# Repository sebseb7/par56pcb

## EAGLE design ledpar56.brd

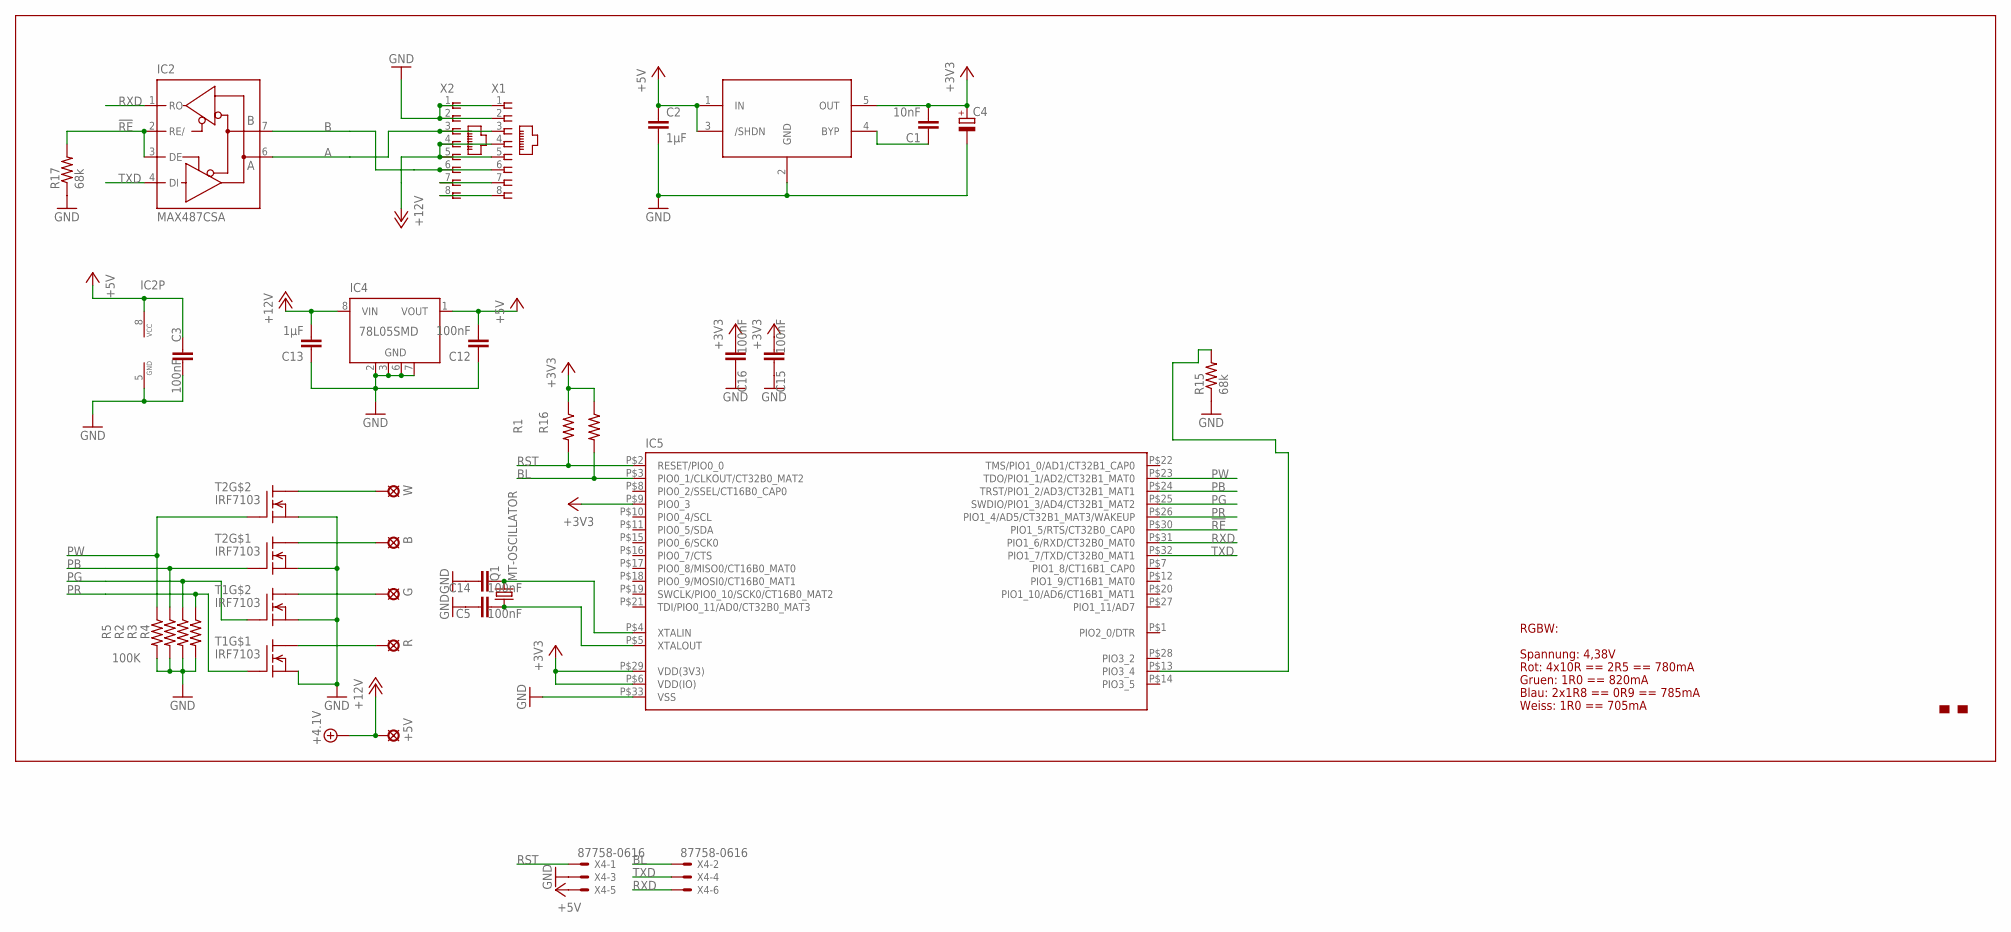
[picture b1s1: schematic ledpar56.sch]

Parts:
+5V: SE14
B: SE14
C1: 10nF; C0402
C2, C13: 1µF; 0805
C3, C5, C12, C14, C15, C16: 100nF; 0402-CAP
C4: CPOL-EUSMCA; SMC_A
G: SE14
IC1: LT1761; SOT23-5L
IC2: MAX487CSA; SO08
IC4: 78L05SMD; SO08
IC5: LPC1113/4_QFN; HVQFN33-7X7
Q1: MT-OSCILLATOR; MT
R: SE14
R1, R2, R3, R4, R5, R16: 100K; 0402-RES
R15, R17: 68k; 0402-RES
T1, T2: IRF7103; SO-8
U$1: MAKE-DD_LOGO'PROMPT'; MAKE-DD_LOGO_PROMPT
W: SE14
X1, X2: RJ45-8L-B; RJ45-NO-SHIELD
X4: 87758-0616

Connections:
!RE: IC2.2 (RE/), IC2.3 (DE), IC5.P$30 (PIO1_5/RTS/CT32B0_CAP0), R17.2
+3V3: C1.2, C4.+, C15.2, C16.2, IC1.5 (OUT), IC5.P$6 (VDD(IO)), IC5.P$9 (PIO0_3), IC5.P$29 (VDD(3V3)), R1.1, R16.1
+5V: C2.1, C3.1, C12.2, IC1.1 (IN), IC1.3 (/SHDN), IC2.8 (VCC), IC4.1 (VOUT), X4.5
+12V: +5V.MP, C13.2, IC4.8 (VIN), X1.4, X1.5, X2.4, X2.5
A: IC2.6 (A), X1.3, X2.3
B: IC2.7 (B), X1.6, X2.6
BL: IC5.P$3 (PIO0_1/CLKOUT/CT32B0_MAT2), R16.2, X4.2
GND: C2.2, C3.2, C4.-, C5.1, C12.1, C13.1, C14.1, C15.1, C16.1, IC1.2 (GND), IC2.5 (GND), IC4.2 (GND), IC4.3 (GND), IC4.6 (GND), IC4.7 (GND), IC5.P$33 (VSS), R2.2, R3.2, R4.2, R5.2, R15.1, R17.1, T1.1 (S), T1.3 (S), T2.1 (S), T2.3 (S), X1.1, X1.2, X2.1, X2.2, X4.3
unnamed: R.MP, T1.8 (D1)
unnamed: T2.5 (D1), W.MP
unnamed: C1.1, IC1.4 (BYP)
unnamed: G.MP, T1.5 (D1)
unnamed: B.MP, T2.8 (D1)
unnamed: IC5.P$13 (PIO3_4), R15.2
unnamed: X1.7, X2.7
unnamed: X1.8, X2.8
unnamed: C5.2, IC5.P$5 (XTALOUT), Q1.1
unnamed: C14.2, IC5.P$4 (XTALIN), Q1.3 (2)
PB: IC5.P$24 (TRST/PIO1_2/AD3/CT32B1_MAT1), R2.1, T2.2 (G)
PG: IC5.P$25 (SWDIO/PIO1_3/AD4/CT32B1_MAT2), R3.1, T1.4 (G)
PR: IC5.P$26 (PIO1_4/AD5/CT32B1_MAT3/WAKEUP), R4.1, T1.2 (G)
PW: IC5.P$23 (TDO/PIO1_1/AD2/CT32B1_MAT0), R5.1, T2.4 (G)
RST: IC5.P$2 (RESET/PIO0_0), R1.2, X4.1
RXD: IC2.1 (RO), IC5.P$31 (PIO1_6/RXD/CT32B0_MAT0), X4.6
TXD: IC2.4 (DI), IC5.P$32 (PIO1_7/TXD/CT32B0_MAT1), X4.4

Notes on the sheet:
RGBW:
Spannung: 4,38V
Rot: 4x10R == 2R5 == 780mA
Gruen: 1R0 == 820mA
Blau: 2x1R8 == 0R9 == 785mA
Weiss: 1R0 == 705mA

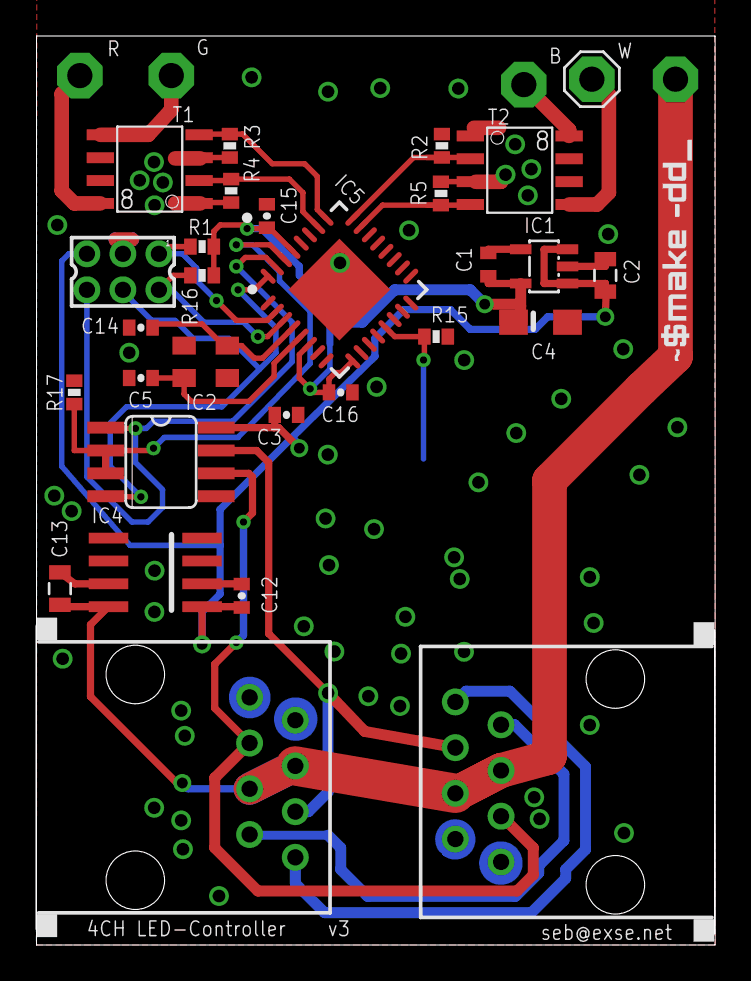
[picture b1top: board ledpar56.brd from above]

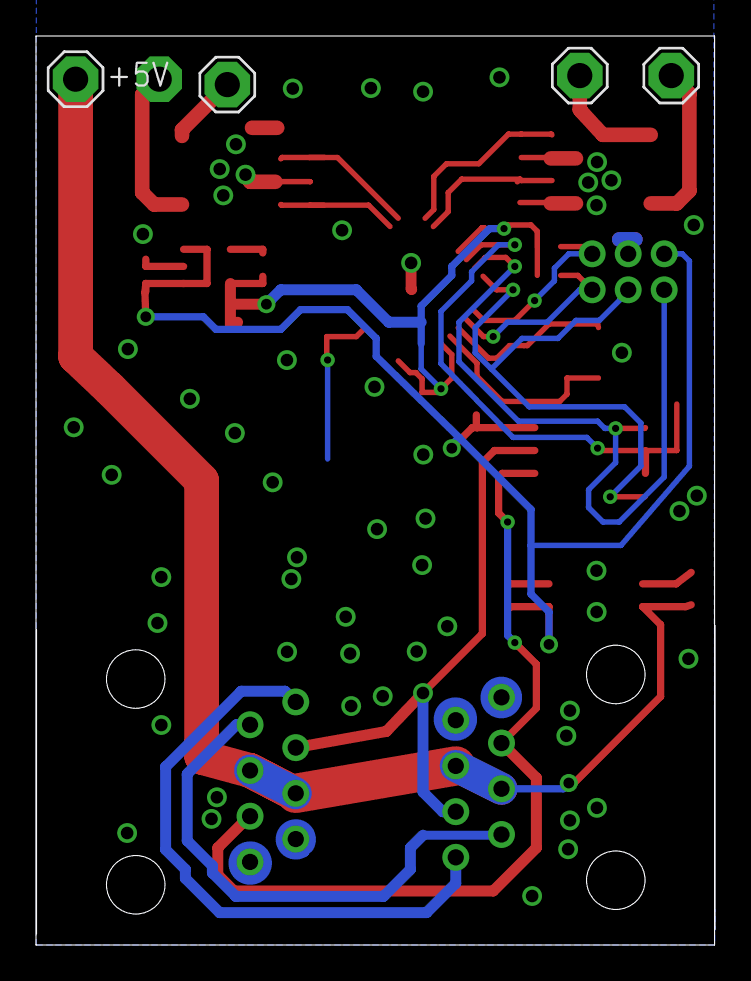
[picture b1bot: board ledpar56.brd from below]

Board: 2 copper layers, 37.7 x 50.5 mm, 34 parts (4 on the bottom side), 25 nets.

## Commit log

2014-02-20 initial

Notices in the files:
parts and their libraries:
microbuilder: This work is placed in the public domain, and may be freely used for commercial and non-commercial work with the following conditions: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
SparkFun-Capacitors: Licensing: CC v3.0 Share-Alike You are welcome to use this library for commercial purposes.
